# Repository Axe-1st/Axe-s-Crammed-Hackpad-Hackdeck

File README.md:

# Axe-s-Crammed-Hackpad-Hackdeck
-This is my own Hackdeck! (maybe i should call it hackdecky)

-If you were wondering why did i make it like this? I made it so i can move more easily in cad than rather keep on holding on my scroll wheel. I plan to add lots of lots of custom presets with its own Firmware and custom app "if i have time thou"

## What it has:
-1x Rotary encoder

-1x 128x32 OLED Display

-4x SK6812 MINI-E LEDs

-8x macro keys (planning to make lots modes/presets)

-worst pcb routing ever

## What it should look like:

-This is My Hackydecky!

-"Please ignore why is there so many colors it should be Black of White!"

-"Also ignore why is the Xiao rp2040 placed on the top layer on the pcb not on the bottom"

-inside

-outside

## PCB:

-2 Layers

-Front

-

-Back

-

## Schematic:

-I had a hard time understanding what a matrix, but in the end some reference photos helped me learn how to. Now my problem is how do i code a matrix :hs: ...

## CAD Files/ CAD Case:

-I made this Case from scratch! 

-I used onshape to make this and i will hate Constraints from now on. 

-I used an STL file of my pcb so i can trace the holes as well.

-Top Part/Cover

-If you noticed why does the top layer have no screw holes?

-Don't worry i have fixed it in my latest commit

-Bottom Part

-as you can see i added cutouts for led and usb port. I also added screw mounting holes

-Made in onshape!

## Firmware:

-So currently right now the firmware i have is for Flashing the leds non stop.

-for sure i will add all of my codes when i start asembly

## BOM:

-Here is all of the Bill of materials to make your own hackdeck as well!

-8x Cherry MX Switches

-8x DSA Keycaps

-4x M3x16mm screws

-4x M3x5mx4mm heatset inserts

-1x Seeed XIAO RP2040

-4x SK6812 MINI-E LEDs

-1x 0.91 inch OLED display

-1x EC11 Rotary encoders

-9x through-hole 1N4148 Diodes

-1x Bottom Case and Cover

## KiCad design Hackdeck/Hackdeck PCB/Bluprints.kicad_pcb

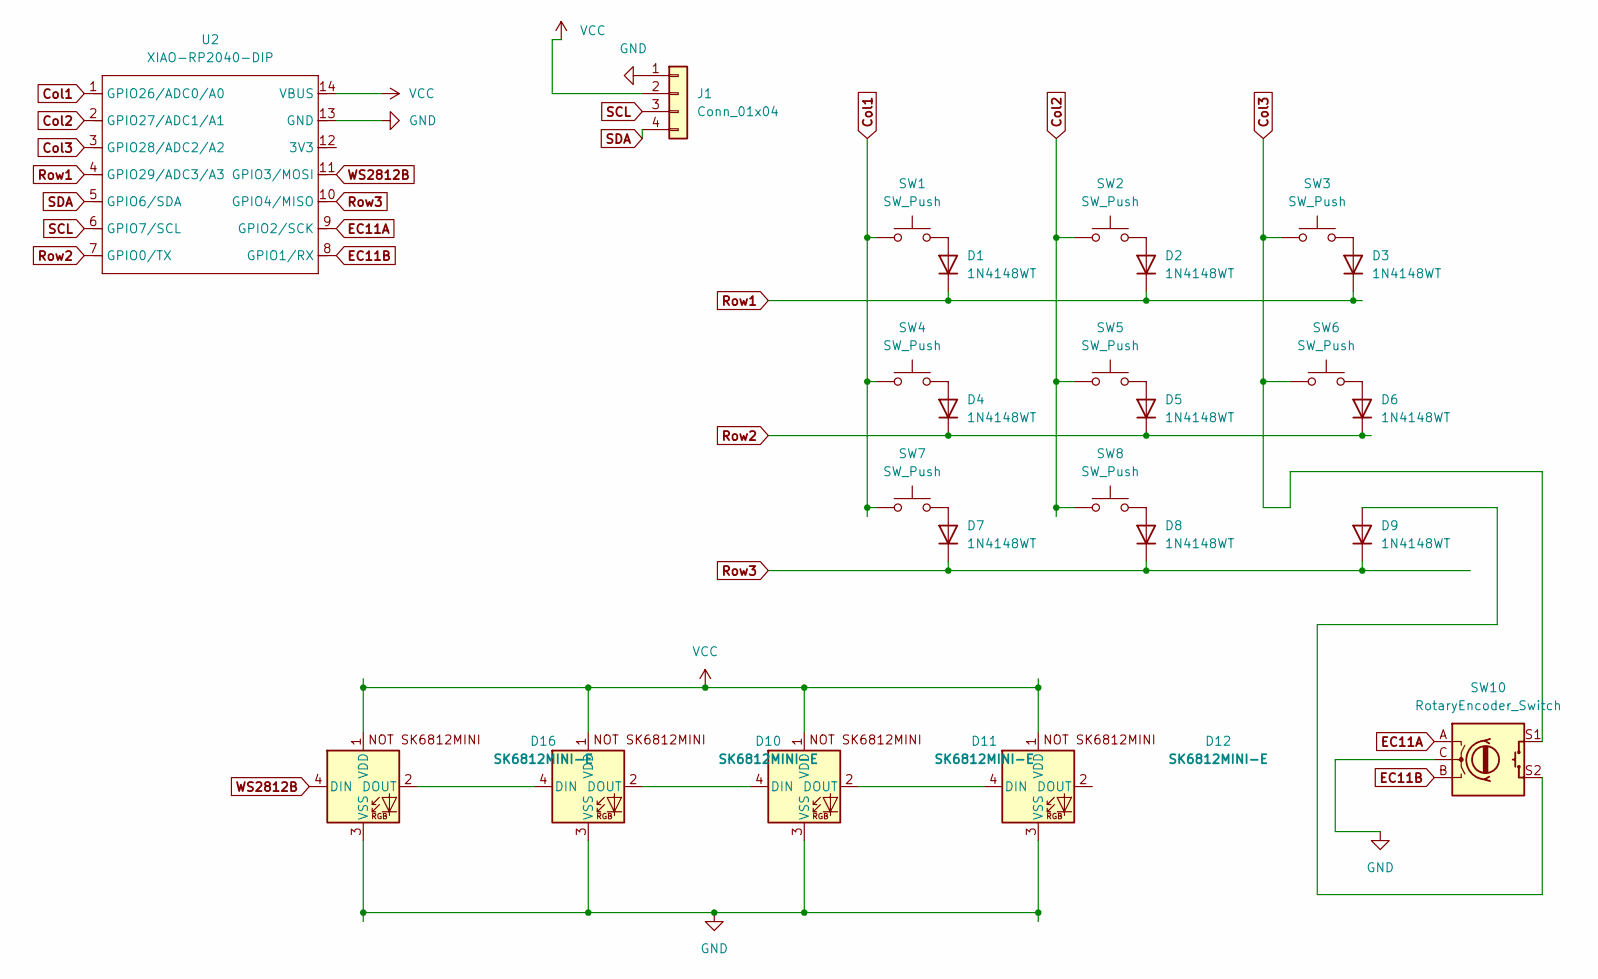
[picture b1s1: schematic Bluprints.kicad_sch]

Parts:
D1, D2, D3, D4, D5, D6, D7, D8, D9: 1N4148WT; D_DO-35_SOD27_P7.62mm_Horizontal
D10, D11, D12, D16: SK6812MINI-E; SK6812MINI-E_fixed
J1: Conn_01x04; SSD1306-0.91-OLED-4pin-128x32
SW1, SW2, SW3, SW4, SW5, SW6, SW7, SW8: SW_Push; SW_Cherry_MX_1.00u_PCB
SW10: RotaryEncoder_Switch; RotaryEncoder_Alps_EC11E-Switch_Vertical_H20mm
U2: XIAO-RP2040-DIP

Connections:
Col1: SW1.1, SW4.1, SW7.1, U2.1 (GPIO26/ADC0/A0)
Col2: SW2.1, SW5.1, SW8.1, U2.2 (GPIO27/ADC1/A1)
Col3: SW3.1, SW6.1, SW10.S1, U2.3 (GPIO28/ADC2/A2)
EC11A: SW10.A, U2.9 (GPIO2/SCK)
EC11B: SW10.B, U2.8 (GPIO1/RX)
GND: D10.3 (VSS), D11.3 (VSS), D12.3 (VSS), D16.3 (VSS), J1.1, SW10.C, U2.13 (GND)
unnamed: D1.2 (A), SW1.2
unnamed: D2.2 (A), SW2.2
unnamed: D3.2 (A), SW3.2
unnamed: D4.2 (A), SW4.2
unnamed: D5.2 (A), SW5.2
unnamed: D6.2 (A), SW6.2
unnamed: D7.2 (A), SW7.2
unnamed: D8.2 (A), SW8.2
unnamed: D9.2 (A), SW10.S2
unnamed: D10.4 (DIN), D16.2 (DOUT)
unnamed: D10.2 (DOUT), D11.4 (DIN)
unnamed: D11.2 (DOUT), D12.4 (DIN)
Row1: D1.1 (K), D2.1 (K), D3.1 (K), U2.4 (GPIO29/ADC3/A3)
Row2: D4.1 (K), D5.1 (K), D6.1 (K), U2.7 (GPIO0/TX)
Row3: D7.1 (K), D8.1 (K), D9.1 (K), U2.10 (GPIO4/MISO)
SCL: J1.3, U2.6 (GPIO7/SCL)
SDA: J1.4, U2.5 (GPIO6/SDA)
VCC: D10.1 (VDD), D11.1 (VDD), D12.1 (VDD), D16.1 (VDD), J1.2, U2.14 (VBUS)
WS2812B: D16.4 (DIN), U2.11 (GPIO3/MOSI)

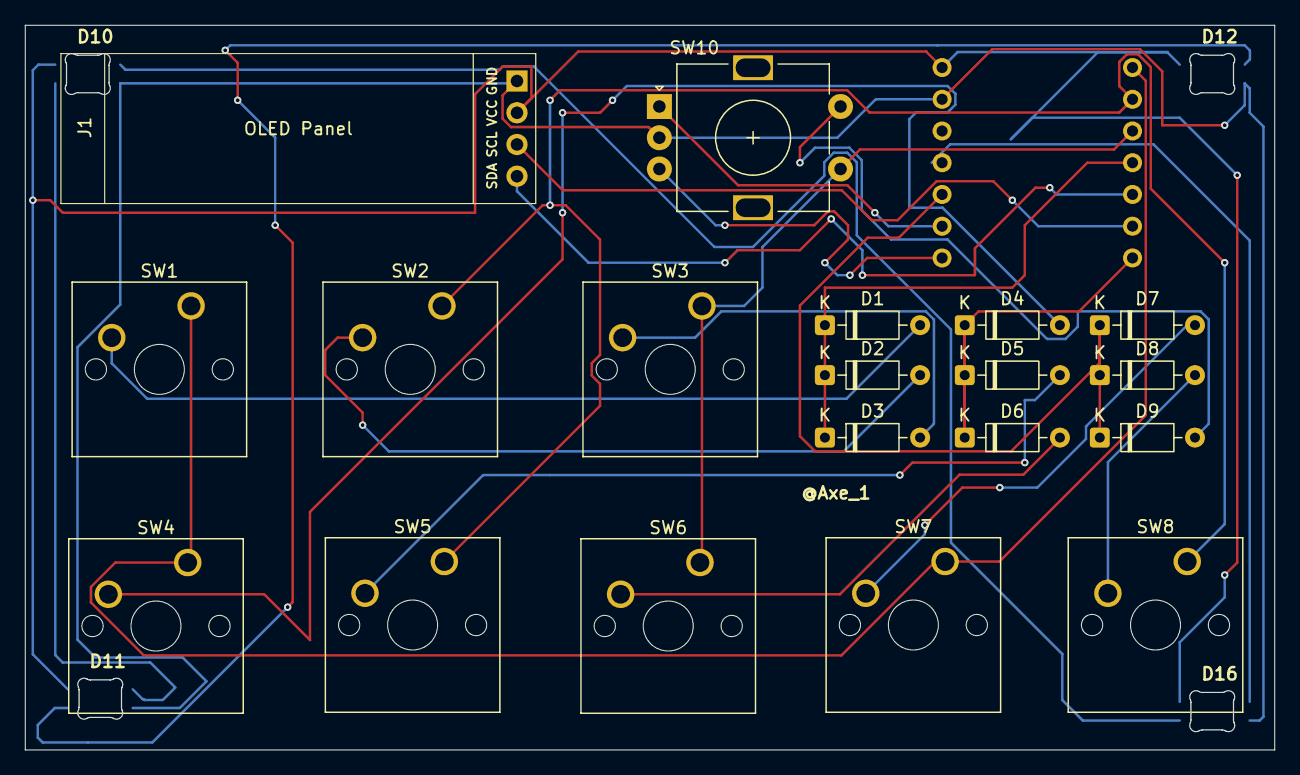
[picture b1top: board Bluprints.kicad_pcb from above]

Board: 2 copper layers, 100.0 x 58.0 mm, 24 parts (1 on the bottom side), 25 nets.

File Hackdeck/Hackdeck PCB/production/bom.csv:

Designator,Footprint,Quantity,Value,LCSC Part #
"D1, D2, D3, D4, D5, D6, D7, D8, D9",D_DO-35_SOD27_P7.62mm_Horizontal,9,1N4148WT,
"D10, D11, D12, D16",SK6812MINI-E_fixed,4,SK6812MINI-E,
J1,SSD1306-0.91-OLED-4pin-128x32,1,Conn_01x04,
"SW1, SW2, SW3, SW4, SW5, SW6, SW7, SW8",SW_Cherry_MX_1.00u_PCB,8,SW_Push,
SW10,RotaryEncoder_Alps_EC11E-Switch_Vertical_H20mm,1,RotaryEncoder_Switch,
U2,XIAO-RP2040-DIP,1,XIAO-RP2040-DIP,

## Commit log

2026-02-11 3 folders first commit
2026-02-11 Fix folders
2026-02-12 light_firmware
2026-02-12 readme
2026-02-12 Update README.md
    Not yet finnished
2026-02-12 Readme_update
2026-02-12 fix imgs
2026-02-12 fix img againnn
2026-02-12 Readme update
2026-02-12 Finalreadme?
2026-02-12 Realfinal.
2026-02-12 Fixed Cad Files also had to update read me to submit
2026-02-12 Updated the images
